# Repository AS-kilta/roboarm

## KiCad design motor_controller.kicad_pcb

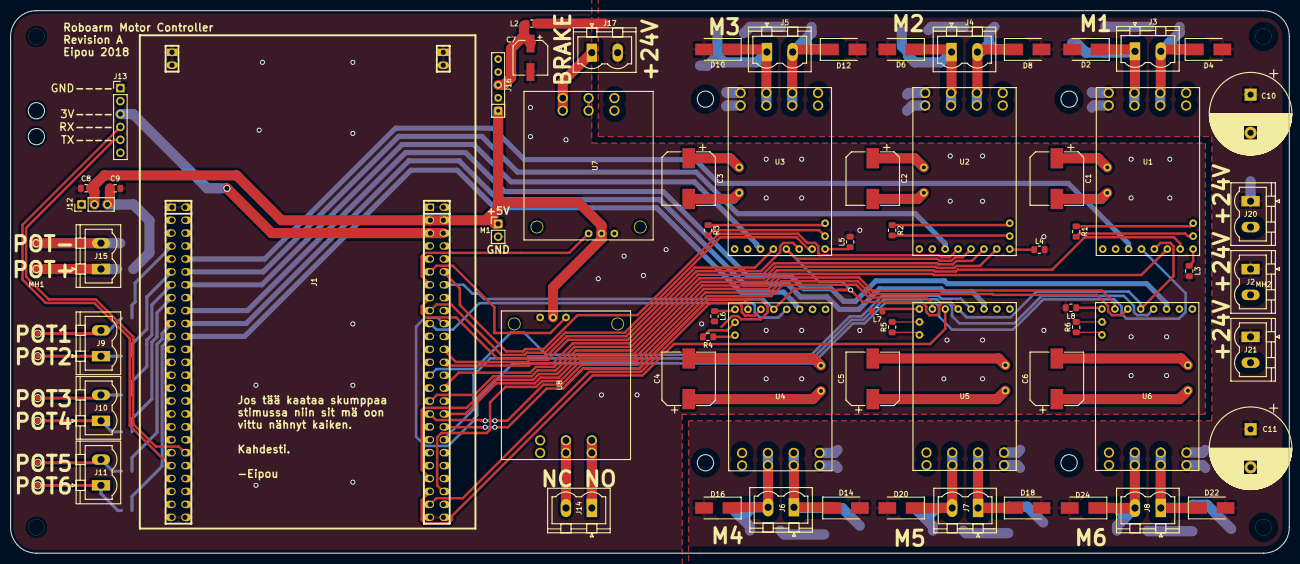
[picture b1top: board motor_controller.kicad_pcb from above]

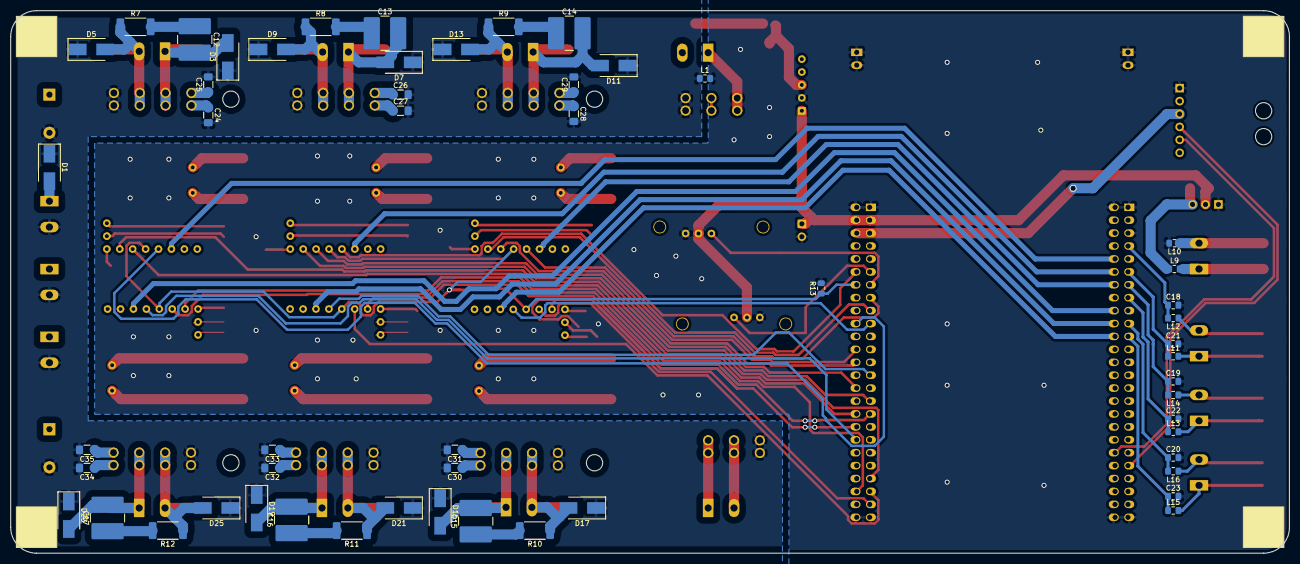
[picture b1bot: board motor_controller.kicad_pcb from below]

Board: 2 copper layers, 251.4 x 106.7 mm, 133 parts (53 on the bottom side), 101 nets.

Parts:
C1, C2, C3, C4, C5, C6: CP; CP_Elec_10x10
C7: 33µ 50V; CP_Elec_6.3x5.9
C8, C9, C18, C19, C20, C21, C22, C23: C; C_0805_2012Metric_Pad1.15x1.40mm_HandSolder
C10, C11: CP; CP_Radial_D16.0mm_P7.50mm
C12, C13, C14, C15, C16, C17: 100n; C_2824_7260Metric_Pad3.20x6.35mm_HandSolder
C24, C25, C26, C27, C28, C29, C30, C31, C32, C33, C34, C35: C; C_1206_3216Metric_Pad1.42x1.75mm_HandSolder
D1, D2, D3, D4, D5, D6, D7, D8, D9, D10, D11, D12, D13, D14, D15, D16, D17, D18, D19, D20, D21, D22, D23, D24, D25: DIODE; D_SMB_Handsoldering
J1: STM32F4_Discovery_Header; stm32f4_discovery_header
J2, J9, J10, J11, J14, J15, J17, J20, J21: Conn_01x02_Male; PhoenixContact_MSTBVA_2,5_2-G-5,08_1x02_P5.08mm_Vertical
J3, J4, J5, J6, J7, J8: Conn_01x02_Female; PhoenixContact_MSTBVA_2,5_2-G-5,08_1x02_P5.08mm_Vertical
J12: Conn_01x03_Male; PinHeader_1x03_P2.54mm_Vertical
J13: Conn_01x06_Male; PinHeader_1x06_P2.54mm_Vertical
J16: pololu-D24V10F5; pololu-d24v10f5
L1, L2: Ferrite_Bead; L_0805_2012Metric_Pad1.15x1.40mm_HandSolder
L3, L4, L5, L6, L7, L8: Ferrite_Bead_Small; L_0805_2012Metric_Pad1.15x1.40mm_HandSolder
L9, L10, L11, L12, L13, L14, L15, L16: Ferrite; L_0805_2012Metric_Pad1.15x1.40mm_HandSolder
M1: Fan; PinHeader_1x02_P2.54mm_Vertical
MH1, MH2: DinMount; controller_din_mount
MH5, MH6, MH7, MH8, MH9, MH10: MountingHole; MountingHole_3.2mm_M3_DIN965
R1, R2, R3, R4, R5, R6: 70k; R_0805_2012Metric_Pad1.15x1.40mm_HandSolder
R7, R8, R9, R10, R11, R12: 100R; R_2512_6332Metric_Pad1.52x3.35mm_HandSolder
R13: 330R; R_0805_2012Metric_Pad1.15x1.40mm_HandSolder
TP1, TP2, TP3, TP4, TP5, TP6, TP7, TP8: TestPoint; TestPoint_Pad_D1.0mm
U1, U2, U3, U4, U5, U6: pololu-g2; pololu_g2_samtec_hpf_hpm
U7, U8: pololu_5v_spdt

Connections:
+5V: C8.1, J1.97, J1.98, J12.2, J16.1, M1.1, U7.2, U8.2
+24V: C10.1, C11.1, C24.1, C25.1, C26.1, C27.1, C28.1, C29.1, C30.1, C31.1, C32.1, C33.1, C34.1, C35.1, D1.2, D2.2, D4.2, D6.2, D8.2, D10.2, D12.2, D14.2, D16.2, D18.2, D20.2, D22.2, D24.2, J2.1, J17.2, J20.1, J21.1, L2.1, U1.14, U2.14, U3.14, U4.14, U5.14, U6.14
GND: C7.2, C8.2, C9.2, C18.2, C19.2, C20.2, C21.2, C22.2, C23.2, J1.1, J1.2, J1.5, J1.23, J1.49, J1.50, J1.51, J1.52, J1.99, J1.100, J12.1, J13.1, J16.2, L1.2, L3.2, L4.2, L5.2, L6.2, L7.2, L8.2, L10.2, M1.2, R13.2, U7.3, U8.3
GNDPWR: C10.2, C11.2, C24.2, C25.2, C26.2, C27.2, C28.2, C29.2, C30.2, C31.2, C32.2, C33.2, C34.2, C35.2, D1.1, D3.1, D5.1, D7.1, D9.1, D11.1, D13.1, D15.1, D17.1, D19.1, D21.1, D23.1, D25.1, J2.2, J20.2, J21.2, L1.1, U1.11, U2.11, U3.11, U4.11, U5.11, U6.11, U7.6, U8.6
unnamed: C1.1, U1.15
unnamed: C1.2, U1.16
unnamed: C2.1, U2.15
unnamed: C2.2, U2.16
unnamed: C3.1, U3.15
unnamed: C3.2, U3.16
unnamed: C4.1, U4.15
unnamed: C4.2, U4.16
unnamed: C5.1, U5.15
unnamed: C5.2, U5.16
unnamed: C6.1, U6.15
unnamed: C6.2, U6.16
unnamed: C7.1, J16.3, L2.2
unnamed: C12.1, R7.2
unnamed: C12.2, D2.1, D3.2, J3.1, U1.13
unnamed: C13.1, R8.2
unnamed: C13.2, D6.1, D7.2, J4.1, U2.13
unnamed: C14.1, R9.2
unnamed: C14.2, D10.1, D11.2, J5.1, U3.13
unnamed: C15.1, R10.2
unnamed: C15.2, D14.1, D15.2, J6.1, U4.13
unnamed: C16.1, R11.2
unnamed: C16.2, D18.1, D19.2, J7.1, U5.13
unnamed: C17.1, R12.2
unnamed: C17.2, D22.1, D23.2, J8.1, U6.13
unnamed: D4.1, D5.2, J3.2, R7.1, U1.12
unnamed: D8.1, D9.2, J4.2, R8.1, U2.12
unnamed: D12.1, D13.2, J5.2, R9.1, U3.12
unnamed: D16.1, D17.2, J6.2, R10.1, U4.12
unnamed: D20.1, D21.2, J7.2, R11.1, U5.12
unnamed: D24.1, D25.2, J8.2, R12.1, U6.12
unnamed: J9.1, L11.2, TP3.1
unnamed: J9.2, L12.1, TP4.1
unnamed: J10.1, L13.2, TP5.1
unnamed: J10.2, L14.1, TP6.1
unnamed: J11.1, L15.2, TP7.1
unnamed: J11.2, L16.1, TP8.1
unnamed: J14.1, U8.4
unnamed: J14.2, U8.5
unnamed: J15.1, L9.2, TP1.1
unnamed: J15.2, L10.1, TP2.1
unnamed: J17.1, U7.4
unnamed: L3.1, U1.8
unnamed: L4.1, U2.8
unnamed: L5.1, U3.8
unnamed: L6.1, U4.8
unnamed: L7.1, U5.8
unnamed: L8.1, U6.8
unnamed: R1.1, U1.10
unnamed: R1.2, U1.9
unnamed: R2.1, U2.10
unnamed: R2.2, U2.9
unnamed: R3.1, U3.10
unnamed: R3.2, U3.9
unnamed: R4.1, U4.10
unnamed: R4.2, U4.9
unnamed: R5.1, U5.10
unnamed: R5.2, U5.9
unnamed: R6.1, U6.10
unnamed: R6.2, U6.9
POT+: C9.1, J12.3, L9.1
VDD: J1.95, J1.96, J13.3
motor_current_1: J1.10, U1.3
motor_current_2: J1.12, U2.3
motor_current_3: J1.14, U3.3
motor_current_4: J1.22, U4.3
motor_current_5: J1.20, U5.3
motor_current_6: J1.18, U6.3
motor_dir_1: J1.69, U1.7
motor_dir_2: J1.72, U2.7
motor_dir_3: J1.83, U3.7
motor_dir_4: J1.66, U4.7
motor_dir_5: J1.67, U5.7
motor_dir_6: J1.68, U6.7
motor_enable_all: J1.88, R13.1, U1.5, U2.5, U3.5, U4.5, U5.5, U6.5
motor_fault_1: J1.82, U1.4
motor_fault_2: J1.90, U2.4
motor_fault_3: J1.85, U3.4
motor_fault_4: J1.81, U4.4
motor_fault_5: J1.73, U5.4
motor_fault_6: J1.64, U6.4
motor_pot_1: C18.1, J1.7, L12.2
motor_pot_2: C21.1, J1.11, L11.1
motor_pot_3: C19.1, J1.13, L14.2
motor_pot_4: C22.1, J1.15, L13.1
motor_pot_5: C20.1, J1.19, L16.2
motor_pot_6: C23.1, J1.21, L15.1
motor_pwm_1: J1.57, U1.6
motor_pwm_2: J1.76, U2.6
motor_pwm_3: J1.78, U3.6
motor_pwm_4: J1.53, U4.6
motor_pwm_5: J1.55, U5.6
motor_pwm_6: J1.56, U6.6
relay_brake: J1.87, U7.1
relay_gripper: J1.89, U8.1
uart_rx: J1.41, J13.4
uart_tx: J1.40, J13.5

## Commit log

2018-09-14 Add project spesific kicad library
2018-09-14 Add kicad project for motor controller
2018-09-19 Add ground vias
2018-09-20 Fix fan mounting hole positions
2018-09-20 Add transient protection for motors
2018-09-21 Add protection for motor controller GND
2018-09-21 Add optional protection for analog inputs
2018-09-21 Add border info to schematic sheets
2018-09-21 Add ceramic capacitors into 24V rail
2018-09-21 Move files to repository root
2018-09-21 Add memes. Also fix silkscreen
2018-09-21 Add no connect symbols to not connected pins
2018-09-21 Add 3d printed parts for controller
2018-09-24 Fix 3D object placements of pololu g2
2018-09-24 Add controller din mount part and 3D model
2018-09-30 Correct POT net names
2018-09-30 Add pulldown to ~motor_sleep_all
2018-09-30 Rename ~motor_sleep to motor_enable
2018-09-30 Change RC-Snubber footprints
2018-09-30 Add TODO, Add fuses to TODO
2018-10-08 Clean schematics, add schematic notes
2018-10-10 Rearrange motor dir pins
    Two of the motor direction pins conflict with JTAG.
